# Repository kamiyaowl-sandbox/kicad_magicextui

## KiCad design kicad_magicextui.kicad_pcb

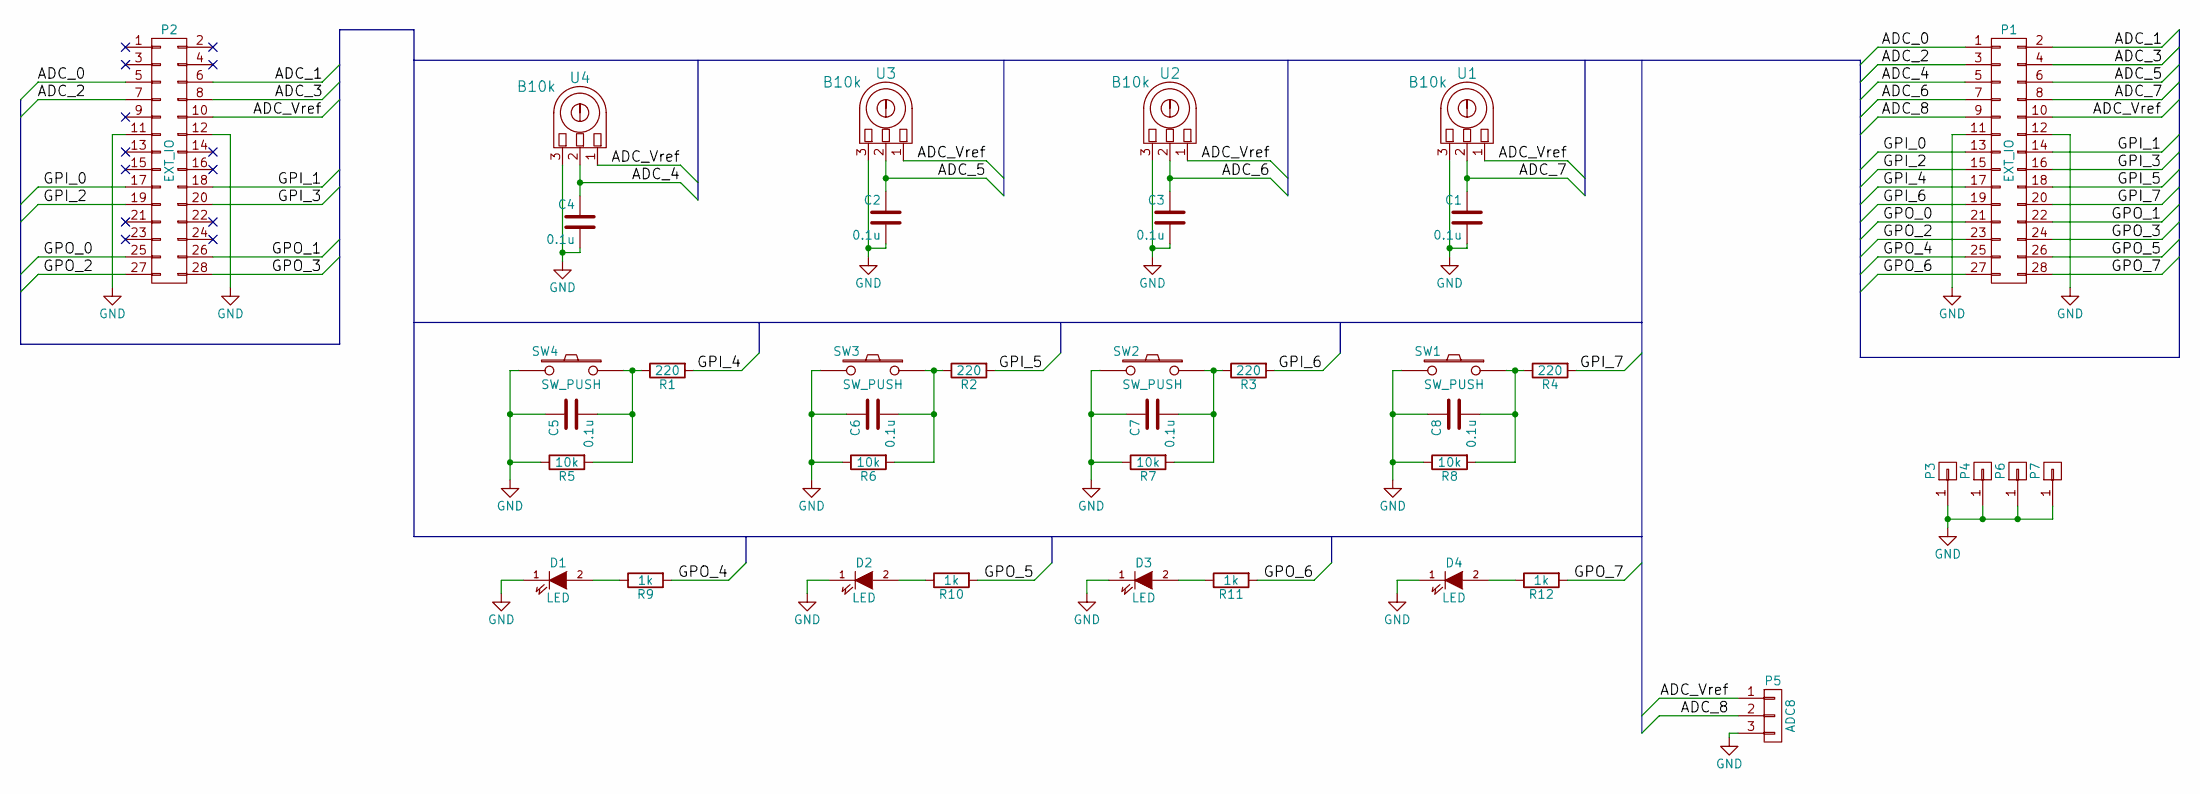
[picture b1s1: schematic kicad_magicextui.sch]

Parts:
C1, C2, C3, C4, C5, C6, C7, C8: 0.1u; C_0402
D1, D2, D3, D4: LED; LED_D5.0mm
P1, P2: EXT_IO; Pin_Header_Straight_2x14_Pitch2.54mm
P3, P4, P6, P7: M3Drill; M3_Drill
P5: ADC8; Pin_Header_Straight_1x03_Pitch2.54mm
R1, R2, R3, R4: 220; R_0603
R5, R6, R7, R8: 10k; R_0603
R9, R10, R11, R12: 1k; R_0603
SW1, SW2, SW3, SW4: SW_PUSH; SW_PUSH-12mm
U1, U2, U3, U4: B10k; Phi6Volume

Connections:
/ADC_0: P1.1, P2.5
/ADC_1: P1.2, P2.6
/ADC_2: P1.3, P2.7
/ADC_3: P1.4, P2.8
/ADC_4: C4.1, P1.5, U4.2
/ADC_5: C2.1, P1.6, U3.2
/ADC_6: C3.1, P1.7, U2.2
/ADC_7: C1.1, P1.8, U1.2
/ADC_8: P1.9, P5.2
/ADC_Vref: P1.10, P2.10, P5.1, U1.1, U2.1, U3.1, U4.1
/GPI_0: P1.13, P2.17
/GPI_1: P1.14, P2.18
/GPI_2: P1.15, P2.19
/GPI_3: P1.16, P2.20
/GPI_4: P1.17, R1.2
/GPI_5: P1.18, R2.2
/GPI_6: P1.19, R3.2
/GPI_7: P1.20, R4.2
/GPO_0: P1.21, P2.25
/GPO_1: P1.22, P2.26
/GPO_2: P1.23, P2.27
/GPO_3: P1.24, P2.28
/GPO_4: P1.25, R9.2
/GPO_5: P1.26, R10.2
/GPO_6: P1.27, R11.2
/GPO_7: P1.28, R12.2
GND: C1.2, C2.2, C3.2, C4.2, C5.1, C6.1, C7.1, C8.1, D1.1 (K), D2.1 (K), D3.1 (K), D4.1 (K), P1.11, P1.12, P2.11, P2.12, P3.1, P4.1, P5.3, P6.1, P7.1, R5.1, R6.1, R7.1, R8.1, SW1.2, SW2.2, SW3.2, SW4.2, U1.3, U2.3, U3.3, U4.3
unnamed: C5.2, R1.1, R5.2, SW4.1
unnamed: C6.2, R2.1, R6.2, SW3.1
unnamed: C7.2, R3.1, R7.2, SW2.1
unnamed: C8.2, R4.1, R8.2, SW1.1
unnamed: D1.2 (A), R9.1
unnamed: D2.2 (A), R10.1
unnamed: D3.2 (A), R11.1
unnamed: D4.2 (A), R12.1

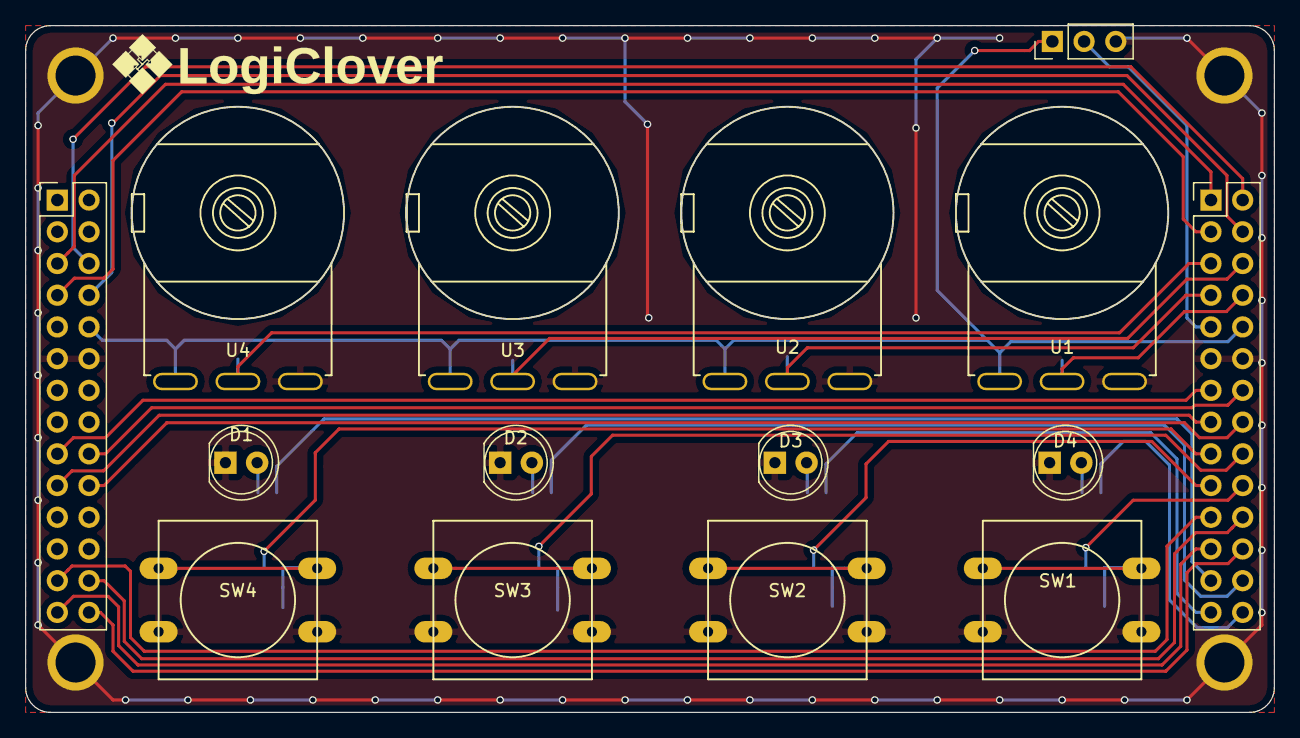
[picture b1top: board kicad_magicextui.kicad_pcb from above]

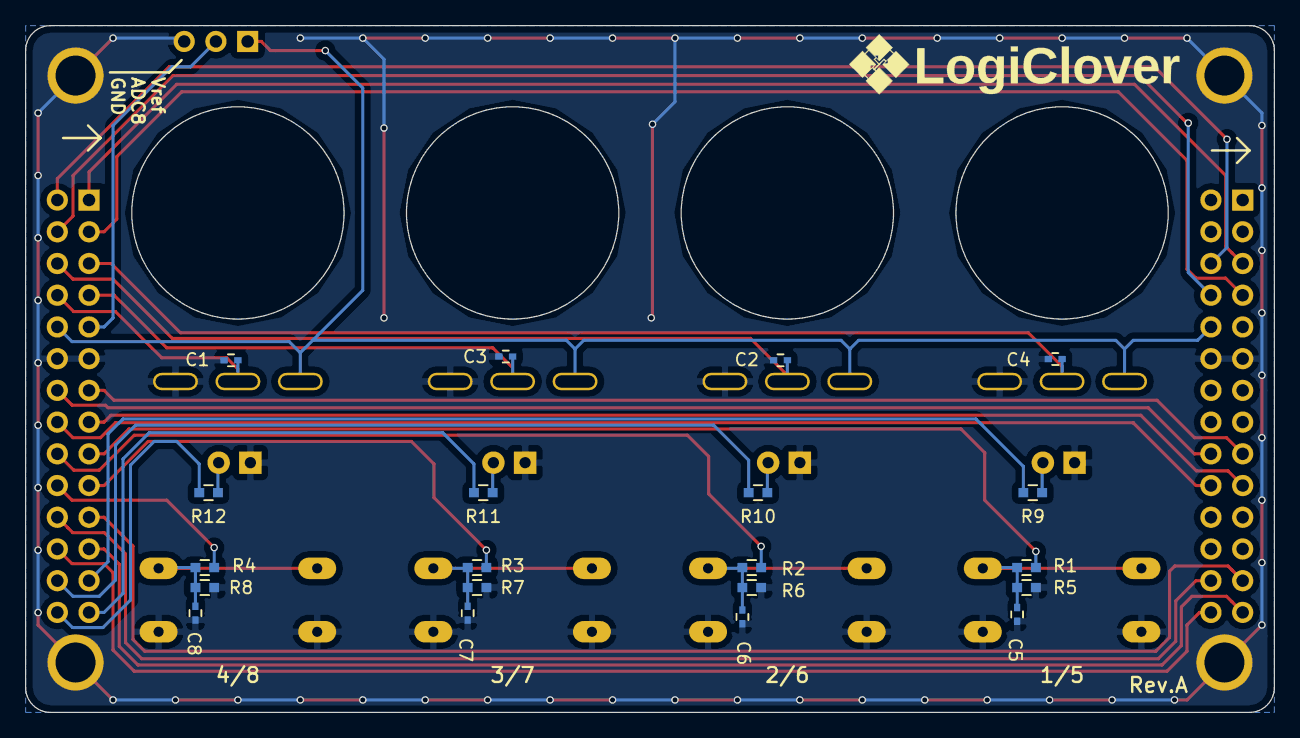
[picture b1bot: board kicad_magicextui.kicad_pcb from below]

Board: 2 copper layers, 100.0 x 55.0 mm, 39 parts (20 on the bottom side), 35 nets.

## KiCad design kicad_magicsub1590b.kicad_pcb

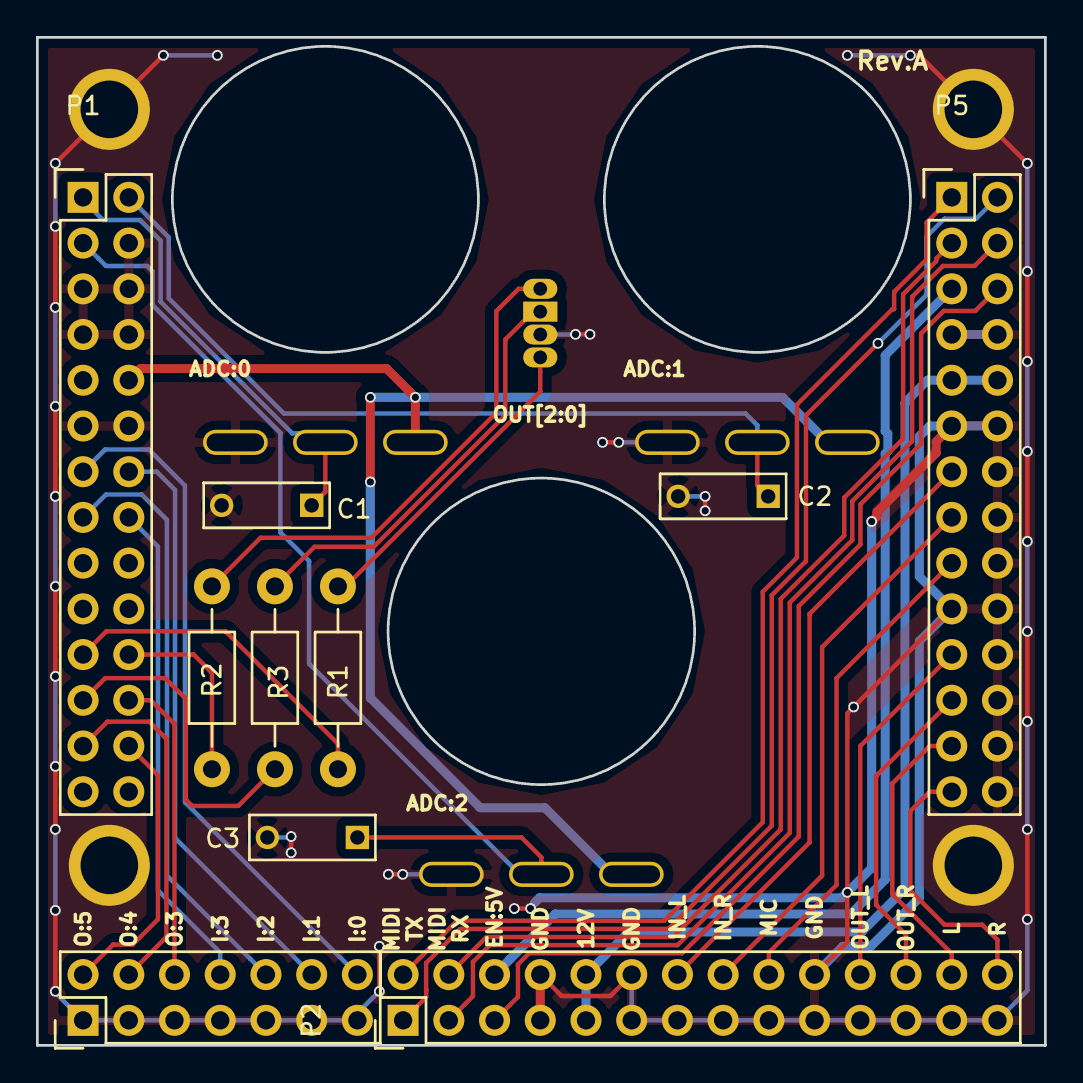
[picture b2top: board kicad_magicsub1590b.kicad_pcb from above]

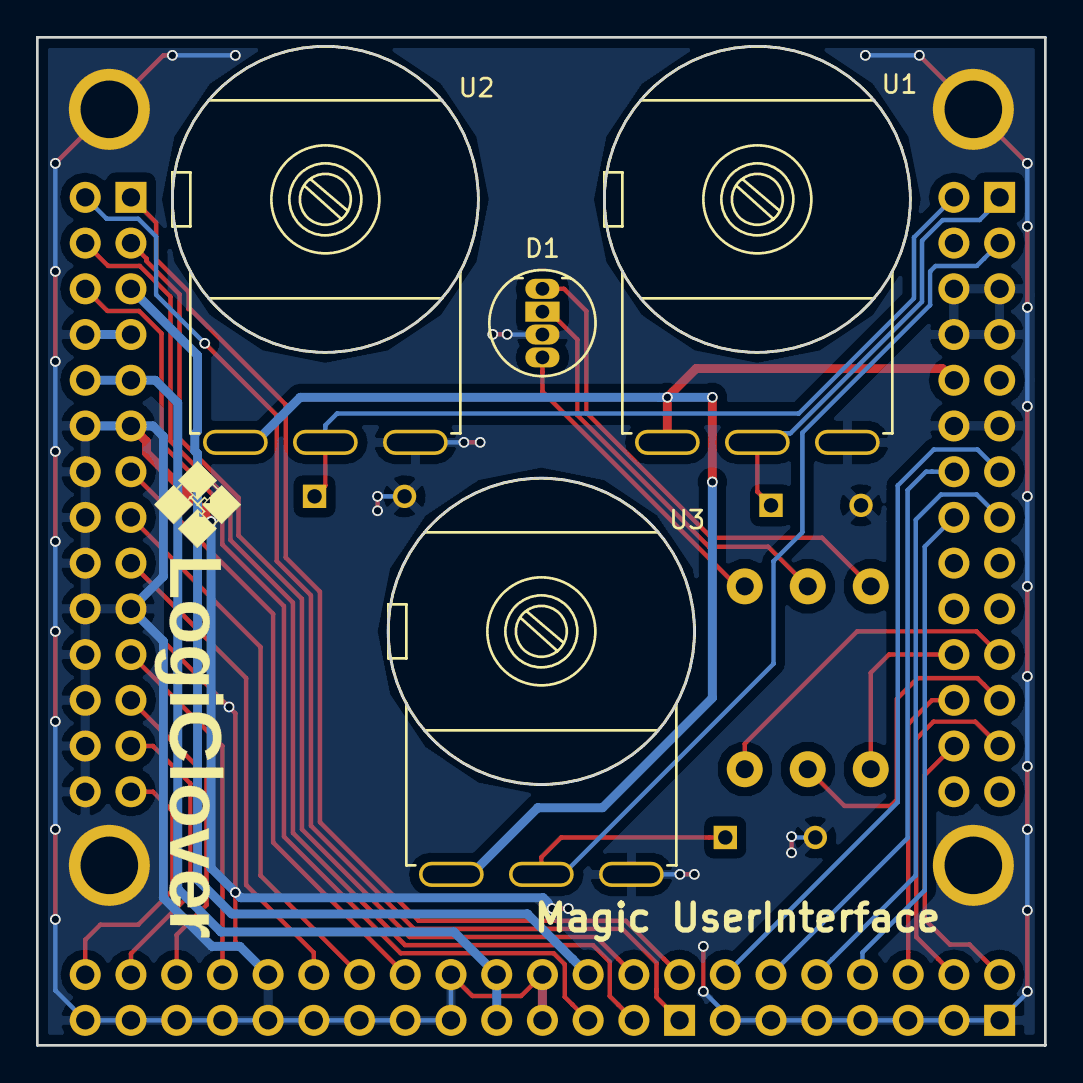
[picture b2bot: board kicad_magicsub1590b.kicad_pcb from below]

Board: 2 copper layers, 56.0 x 56.0 mm, 18 parts (4 on the bottom side), 32 nets.

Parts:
C1, C2, C3: 0.1u; C_Rect_L7_W2.5_P5
D1: OSTA5131A-R/PG/B; LED-RGB-5MM_Common_Cathode
P1, P2, P5: EXT_IO; Pin_Header_Straight_2x14
P3, P4, P6, P7: M3Drill; M3_Drill
P8: EXT_IO; Pin_Header_Straight_2x07
R1: 1k2; Resistor_Horizontal_RM10mm
R2, R3: 200; Resistor_Horizontal_RM10mm
U1, U2, U3: B10k; Phi6Volume

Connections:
+5V: P2.6, P5.5
+12V: P2.9, P2.10, P5.9, P5.10
/ADC_0: C1.1, P1.1, U1.2
/ADC_1: C2.1, P1.2, U2.2
/ADC_2: C3.1, P1.3, U3.2
/ADC_Vref: P1.10, U1.1, U2.1, U3.1
/EN_5V: P2.5, P5.6
/GPI_0: P1.13, P8.14
/GPI_1: P1.14, P8.12
/GPI_2: P1.15, P8.10
/GPI_3: P1.16, P8.8
/GPO_0: P1.21, R1.2
/GPO_1: P1.22, R2.2
/GPO_2: P1.23, R3.2
/GPO_3: P1.24, P8.6
/GPO_4: P1.25, P8.4
/GPO_5: P1.26, P8.2
/HP_OUT_L: P2.26, P5.25
/HP_OUT_R: P2.28, P5.27
/LINE_IN_L: P2.14, P5.13
/LINE_IN_R: P2.16, P5.15
/LINE_OUT_L: P2.22, P5.21
/LINE_OUT_R: P2.24, P5.23
/MIC_IN: P2.18, P5.17
/MIDI_RX_4: P2.4, P5.3
/MIDI_RX_5: P2.3, P5.4
/MIDI_TX_4: P2.2, P5.1
/MIDI_TX_5: P2.1, P5.2
GND: C1.2, C2.2, C3.2, D1.3, P1.4, P1.5, P1.6, P1.7, P1.8, P1.11, P1.12, P2.7, P2.8, P2.11, P2.12, P2.13, P2.15, P2.17, P2.19, P2.20, P2.21, P2.23, P2.25, P2.27, P3.1, P4.1, P5.7, P5.8, P5.11, P5.12, P5.14, P5.16, P5.18, P5.19, P5.20, P5.22, P5.24, P5.26, P5.28, P6.1, P7.1, P8.1, P8.3, P8.5, P8.7, P8.9, P8.11, P8.13, U1.3, U2.3, U3.3
unnamed: D1.1, R2.1
unnamed: D1.2, R3.1
unnamed: D1.4, R1.1

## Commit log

2016-12-17 配線引いた
2017-01-22 つくった
